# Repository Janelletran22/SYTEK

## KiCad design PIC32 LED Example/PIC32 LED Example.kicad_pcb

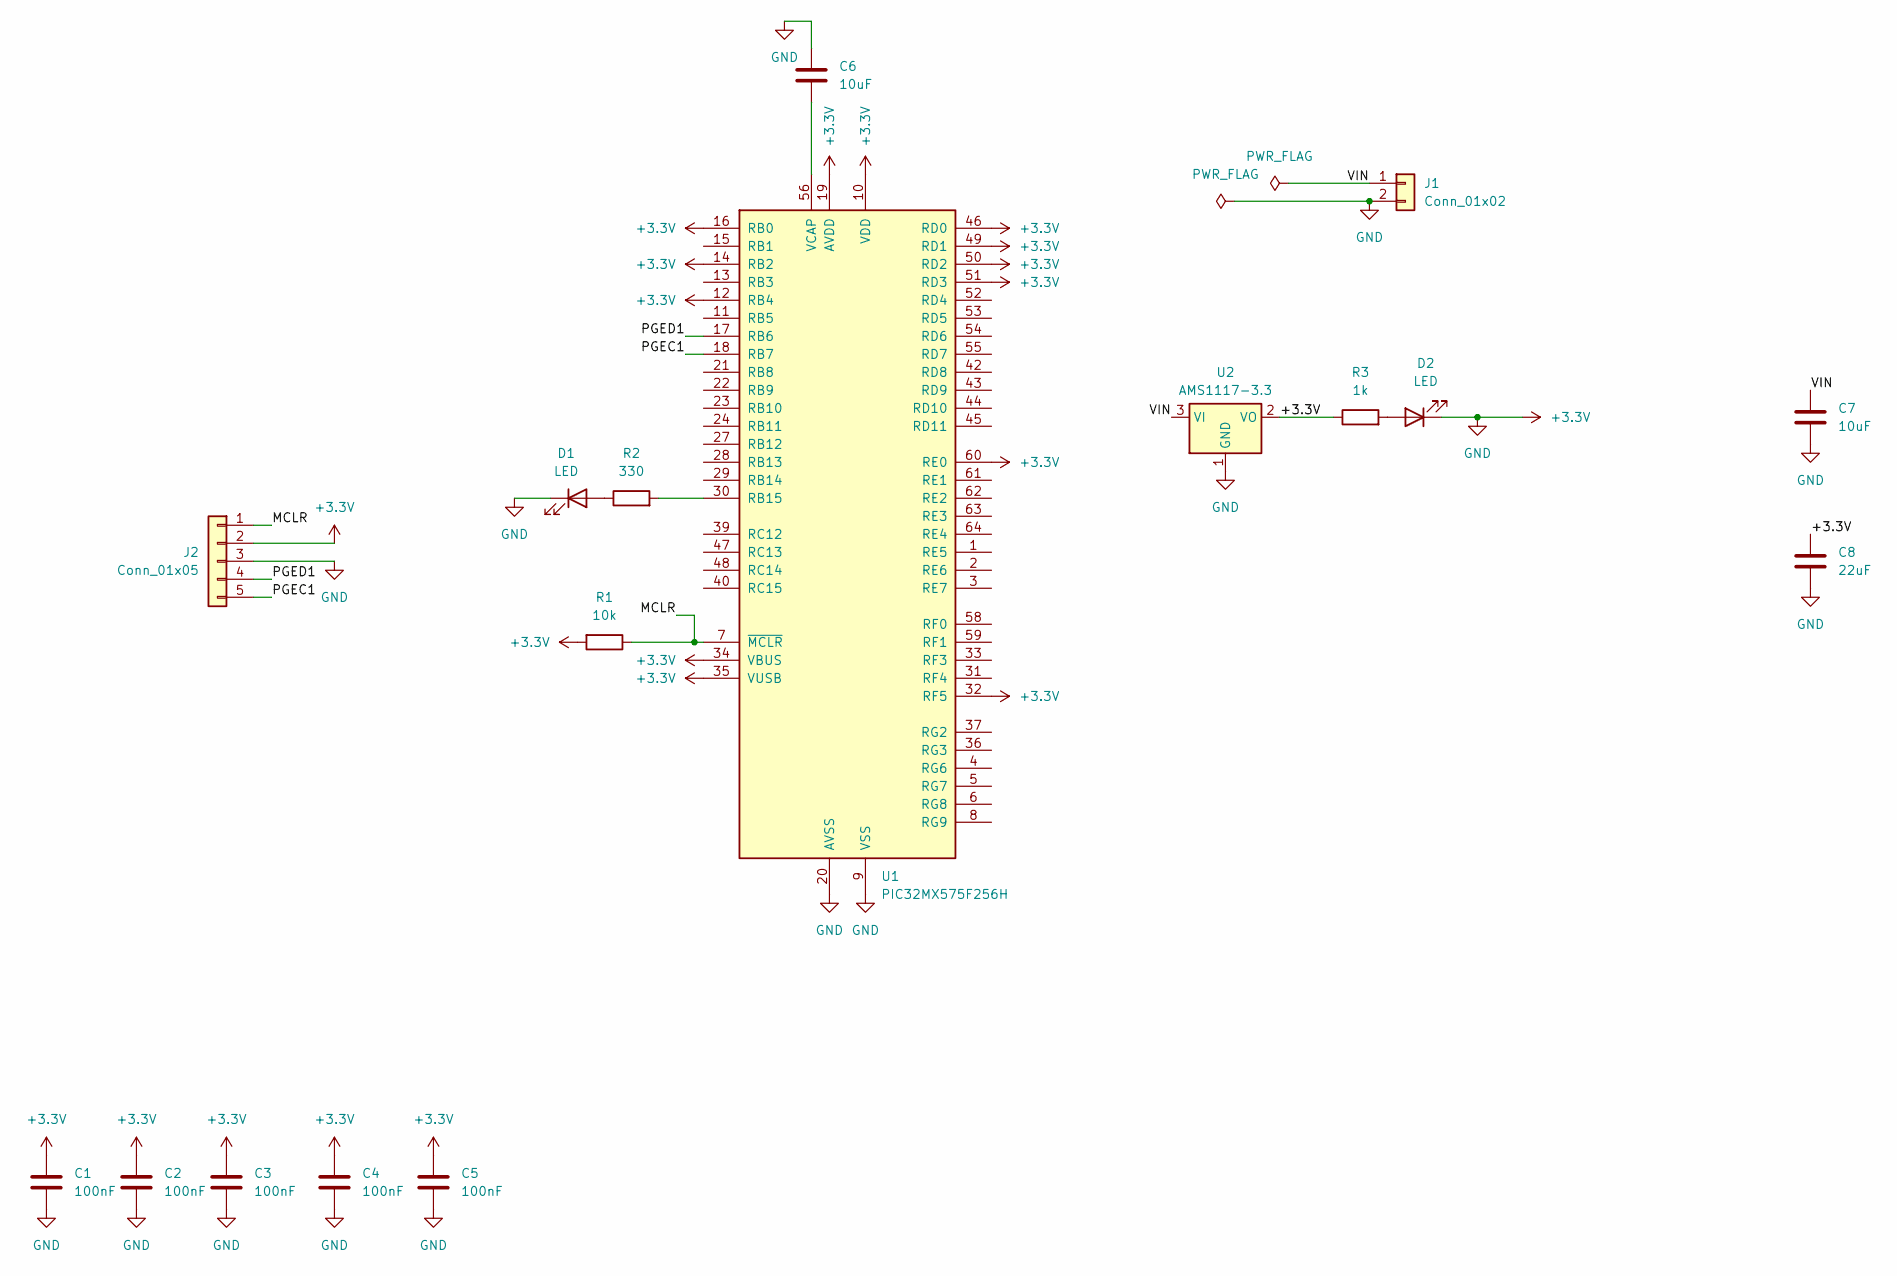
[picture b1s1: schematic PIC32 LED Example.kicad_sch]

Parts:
C1, C2, C3, C4, C5: 100nF; C_0805_2012Metric
C6, C7: 10uF; C_0805_2012Metric
C8: 22uF; C_1206_3216Metric
D1, D2: LED; LED_0805_2012Metric
J1: Conn_01x02; PinHeader_1x02_P2.54mm_Vertical
J2: Conn_01x05; PinHeader_1x05_P2.54mm_Vertical
R1: 10k; R_0805_2012Metric
R2: 330; R_0805_2012Metric
R3: 1k; R_0805_2012Metric
U1: PIC32MX575F256H; LQFP-64_10x10mm_P0.5mm
U2: AMS1117-3.3; SOT-223-3_TabPin2

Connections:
+3.3V: C1.1, C1.2, C2.1, C2.2, C3.1, C3.2, C4.1, C4.2, C5.1, C5.2, C6.1, C7.2, C8.1, C8.2, D1.1 (K), D2.1 (K), J1.2, J2.2, J2.3, R1.2, R3.1, U1.9 (VSS), U1.10 (VDD), U1.12 (RB4), U1.14 (RB2), U1.16 (RB0), U1.19 (AVDD), U1.20 (AVSS), U1.25 (VSS), U1.26 (VDD), U1.32 (RF5), U1.34 (VBUS), U1.35 (VUSB), U1.38 (VDD), U1.41 (VSS), U1.46 (RD0), U1.49 (RD1), U1.50 (RD2), U1.51 (RD3), U1.57 (VDD), U1.60 (RE0), U2.1 (GND), U2.2 (VO)
/MCLR: J2.1, R1.1, U1.7 (~MCLR)
/PGEC1: J2.5, U1.18 (RB7)
/PGED1: J2.4, U1.17 (RB6)
/VIN: C7.1, J1.1, U2.3 (VI)
unnamed: D1.2 (A), R2.1
unnamed: D2.2 (A), R3.2
unnamed: R2.2, U1.30 (RB15)
unnamed: C6.2, U1.56 (VCAP)

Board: 2 copper layers, 17 parts (0 on the bottom side), 9 nets, no tracks yet.

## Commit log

2025-12-10 finished ERC approved PIC32 LED example
2025-12-10 PCB placement
